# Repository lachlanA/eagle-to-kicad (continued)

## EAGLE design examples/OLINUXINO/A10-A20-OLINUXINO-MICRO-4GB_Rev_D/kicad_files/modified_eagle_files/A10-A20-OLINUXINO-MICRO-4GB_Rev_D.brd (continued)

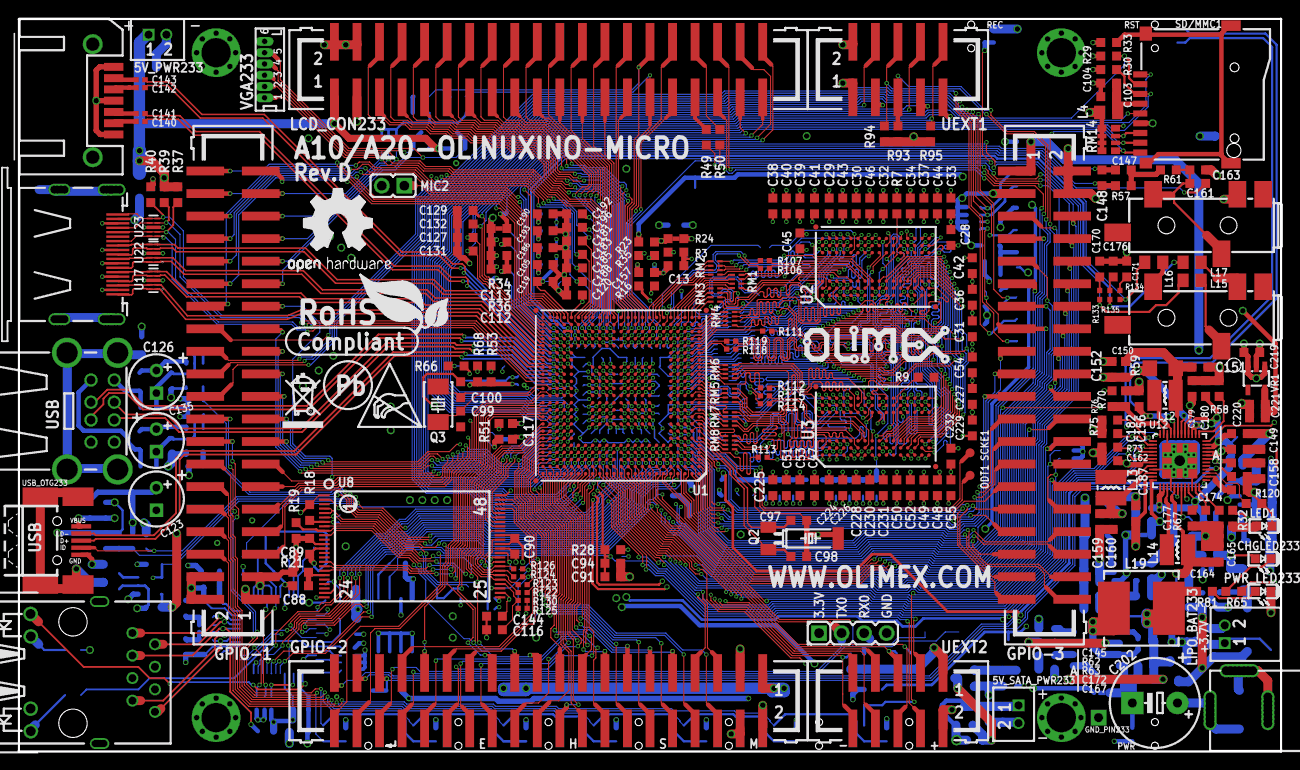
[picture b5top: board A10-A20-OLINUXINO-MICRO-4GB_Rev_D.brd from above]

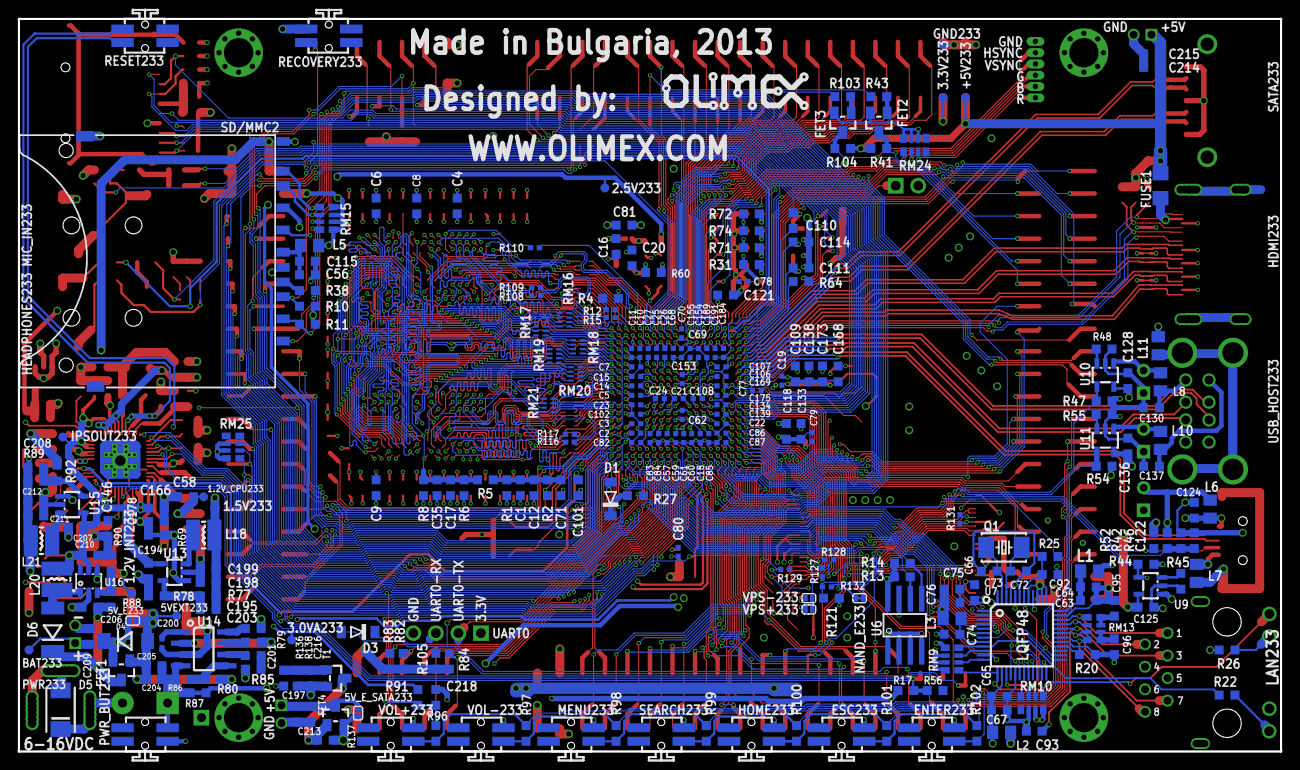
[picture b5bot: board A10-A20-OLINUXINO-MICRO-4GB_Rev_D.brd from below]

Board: 4 copper layers, 142.2 x 82.6 mm, 558 parts (271 on the bottom side), 539 nets.

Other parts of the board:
U$5: LOGO-OPENHARDWARE_8X8
U$6, U$8: OLIMEX1_V
U$9: PB
U$10: ESD_SYMBOL
U$11: RECYCLE_BIN1/8
U$12: ROHS

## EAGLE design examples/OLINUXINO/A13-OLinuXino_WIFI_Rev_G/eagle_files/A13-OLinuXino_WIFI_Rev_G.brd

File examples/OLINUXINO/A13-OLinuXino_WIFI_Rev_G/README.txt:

NOTE: ***** USE AT YOUR OWN RISK *****

This contains the eagle file's from OLIMEX/OLINUXINO from github, which have been Renumbered to work with KiCad
as KiCad will not work correctly with out parts reference ending in a number.
Also note the Eagle files have been converted to version 6.xx of eagle.

*** NOTE: you have to enable LIB prifix in the eagle6xx-sch-to-kicad-sch.ulp even thou is shows you don't need it.
          for some reson Ealge has a lib part which has the same name, as the ground part,  but dose not show up
          when the script searchs for conflicking part names, but show's up on the lib !!!  go figure !!!  ****

source of this project example is at Github address:
   https://github.com/OLIMEX/OLINUXINO/tree/master/HARDWARE/A13-OLinuXino

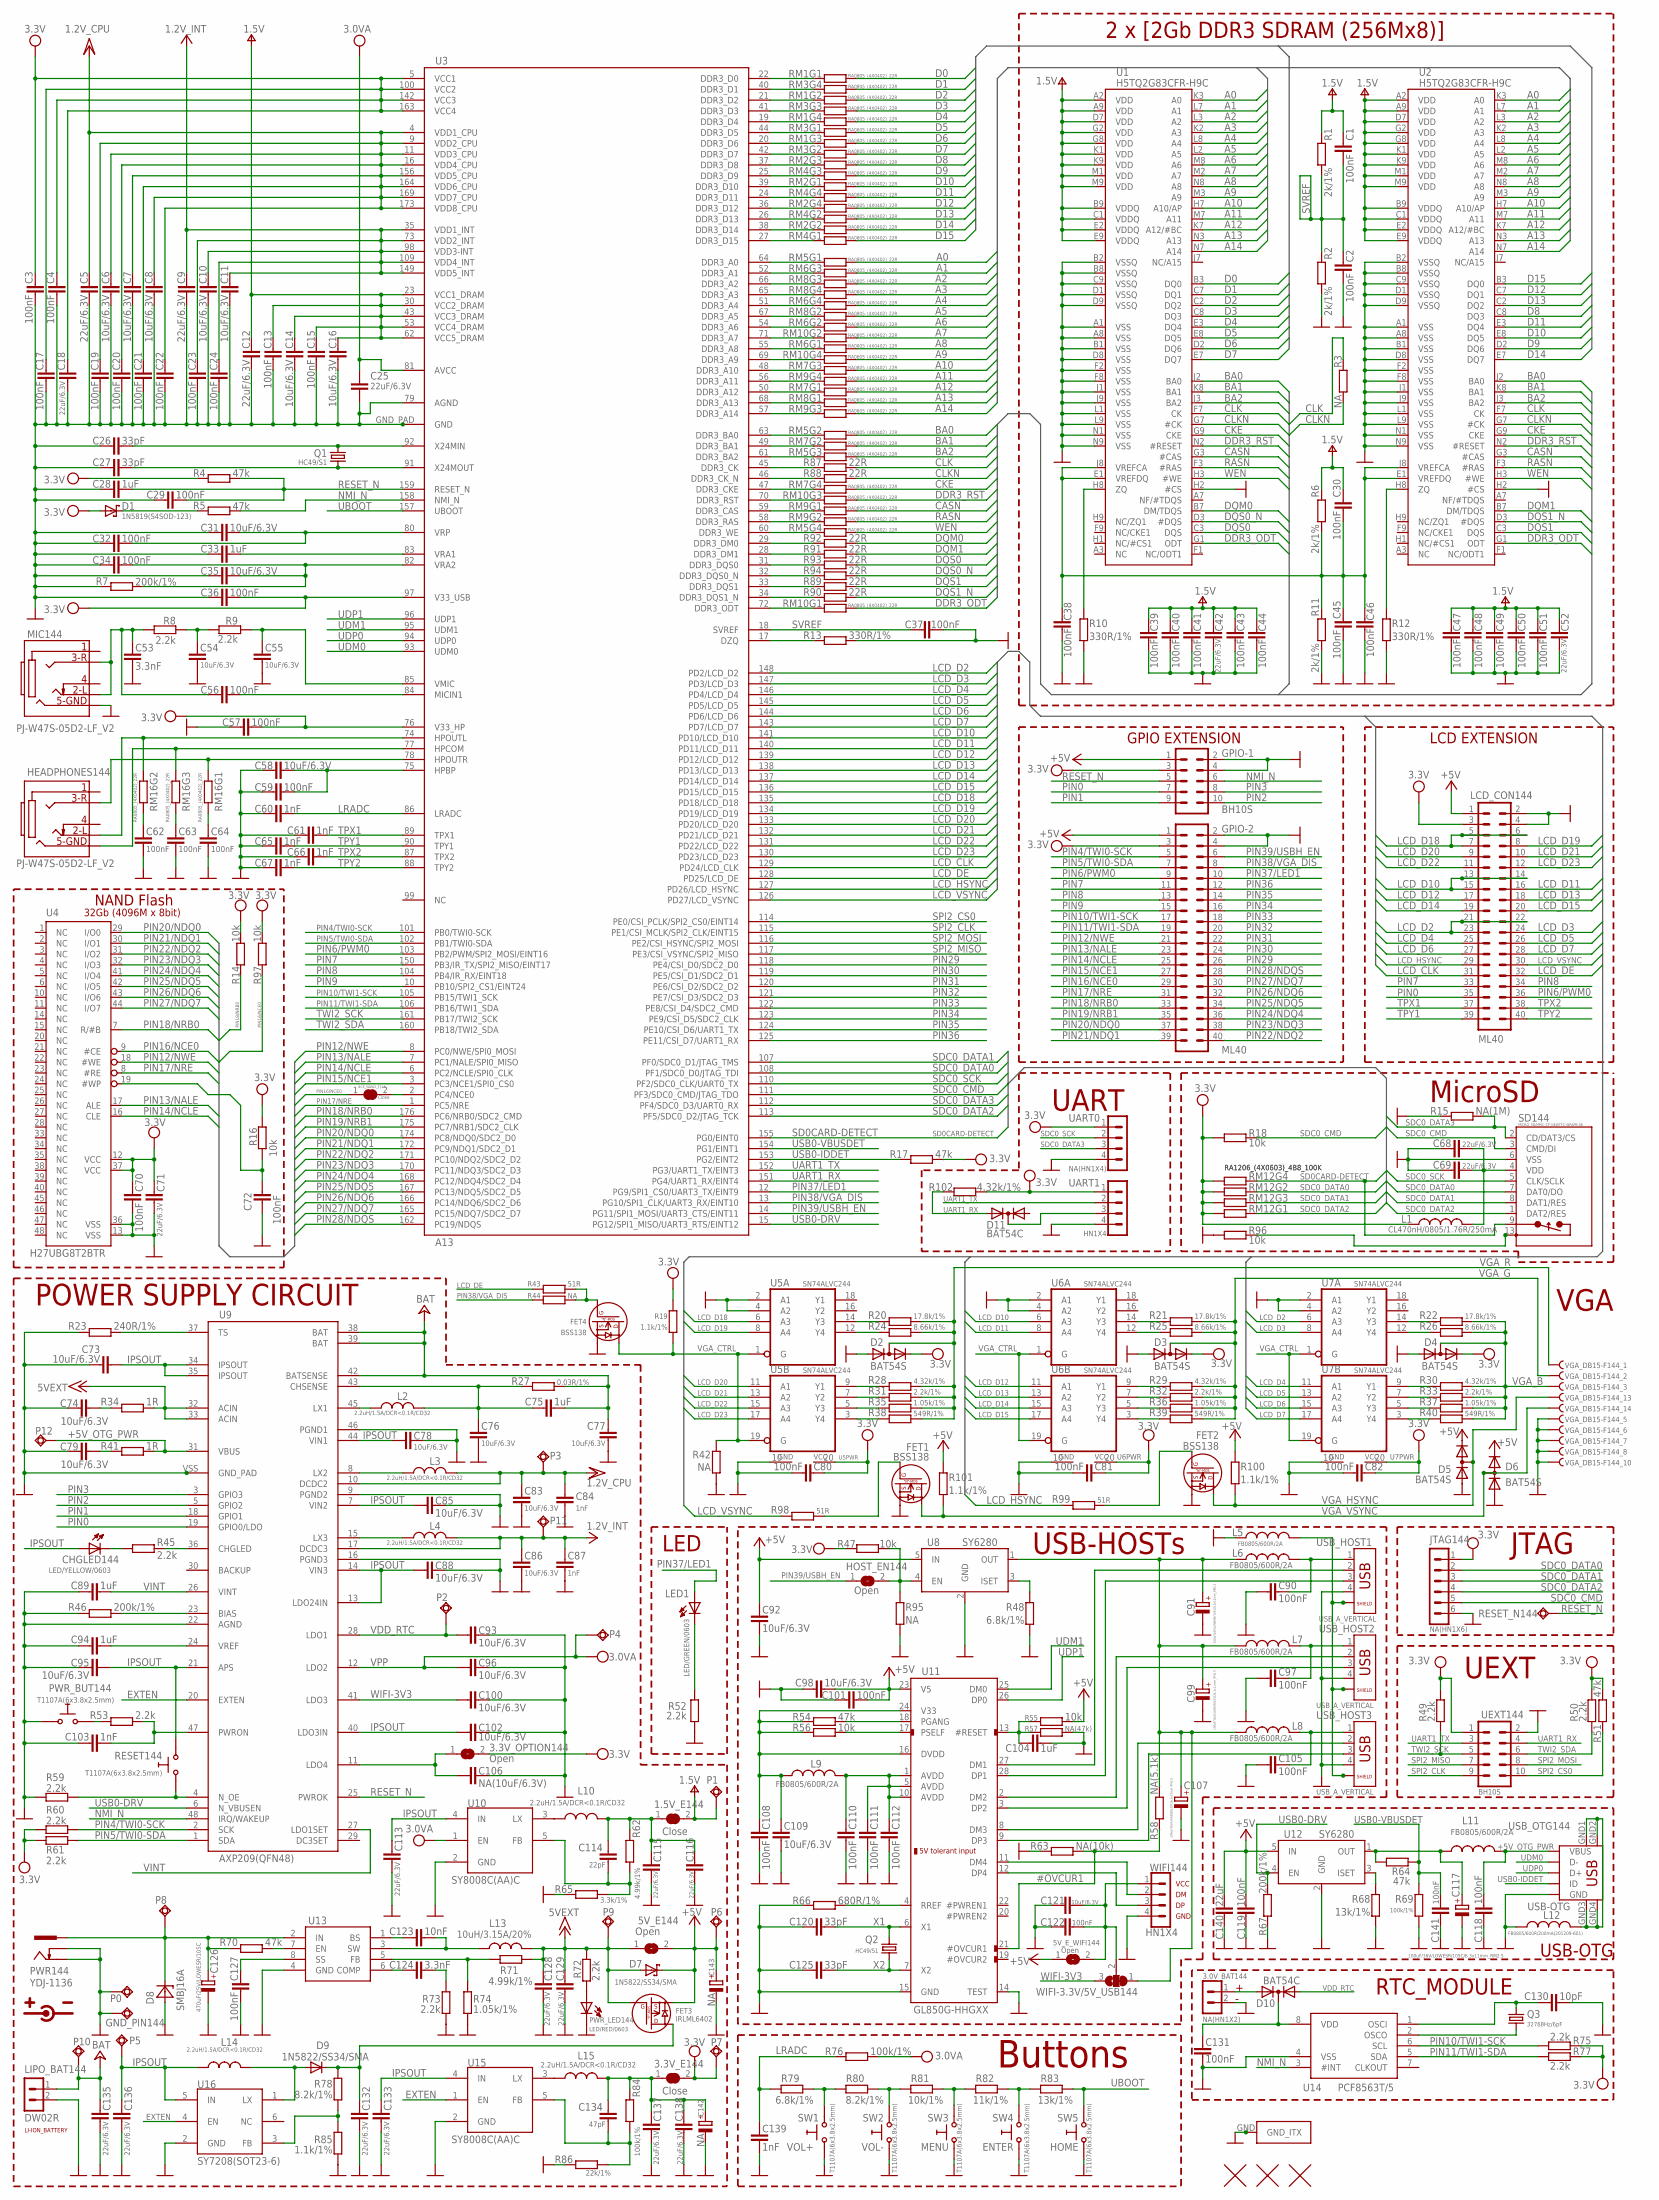
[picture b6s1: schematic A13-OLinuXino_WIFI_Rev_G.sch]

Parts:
1.5V_E144, 3.3V_E144: Close; SJ_1_SMALLER_CLOSE
3.0V_BAT144: NA(HN1X2); HN1X2
3.3V_OPTION144, 5V_E144, 5V_E_WIFI144: Open; SJ_1_SMALLER
#CE_NAND_E144: Close; SJ_1_SMALLER_CLOSE_10MILS
C1, C2, C3, C4, C13, C15, C17, C19, C20, C21, C22, C23, C24, C29, C30, C32, C34, C36, C37, C38, C39, C40, C41, C43, C44, C45, C46, C47, C48, C49, C50, C51, C56, C57, C59, C62, C63, C64, C70, C72, C80, C81, C82, C90, C97, C101, C105, C108, C110, C111, C112, C118, C119, C122, C127, C131, C141: 100nF; C0603_DWS
C5, C9, C12, C18, C25, C42, C52, C68, C69, C71, C113, C115, C116, C128, C129, C132, C133, C135, C136, C137, C138: 22uF/6.3V; C0603_DWS
C6, C7, C8, C10, C11, C14, C16, C31, C35, C54, C55, C58, C73, C74, C76, C77, C78, C79, C83, C85, C86, C88, C92, C93, C95, C96, C98, C100, C102, C109, C121: 10uF/6.3V; C0603_DWS
C26, C27, C120, C125: 33pF; C0603_DWS
C28, C33, C75, C89, C94, C104: 1uF; C0603_DWS
C53, C124: 3.3nF; C0603_DWS
C60, C61, C65, C66, C67, C84, C87, C103, C139: 1nF; C0603_DWS
C91, C99, C107, C117: 100uF/16V/LOWESR/105C/6.3x11mm_RM2.5; E2,5-6,3
C106: NA(10uF/6.3V); C0603_DWS
C114: 22pF; C0603_DWS
C123: 10nF; C0603_DWS
C126: 470uF/25V/LOWESR/105C; E5-10,5
C130: 10pF; C0603_DWS
C134: 47pF; C0603_DWS
C140: 22uF; C0603_DWS
C142, C143: NA; E3,5-8
CHGLED144: LED/YELLOW/0603; LED-0603
D1: 1N5819(S4SOD-123); SOD-123
D2, D3, D4, D5, D6: BAT54S; SOT23C(BAT54S)
D7: 1N5822/SS34/SMA; MLL-41
D8: SMBJ16A; DO214AA
D9: 1N5822/SS34/SMA; MELF-MLL41
D10, D11: BAT54C; SOT23C
FET1, FET2, FET4: BSS138; SOT23
FET3: IRLML6402; SOT23
GND_PIN144: TESTPAD3; TEST_PAD40/70/SQUARE
GPIO-1: BH10S; ML10-MALE
GPIO-2: ML40
HEADPHONES144: PJ-W47S-05D2-LF_V2; PJ-W47S-05D2-LF_5PIN_V2
HOST_EN144: Open; SJ_1_SMALLER
JTAG144: NA(HN1X6); HN1X6
L1: CL470nH/0805/1.76R/250mA; L0805_5MIL_DWS
L2, L3, L4, L10, L14, L15: 2.2uH/1.5A/DCR<0.1R/CD32; CD32
L5, L6, L7, L8, L9, L11: FB0805/600R/2A; L0805_5MIL_DWS
L12: FB0805/600R/200mA(201209-601); L0805_5MIL_DWS
L13: 10uH/3.15A/20%; 8X8MM_3131
LCD_CON144: ML40
LED1: LED/GREEN/0603; LED-0603
LIPO_BAT144: DW02R
MIC144: PJ-W47S-05D2-LF_V2; PJ-W47S-05D2-LF_5PIN_V2
P0, P1, P2, P3, P4, P5, P6, P7, P8, P9, P10, P11, P12: TESTPADTESTPAD_40-ROUND; TESTPAD_40-ROUND
PWR144: YDJ-1136; PWR_JACK_UNI_MILLING
PWR_BUT144: T1107A(6x3.8x2.5mm); SW-TAKT_6X3.5_SMD
PWR_LED144: LED/RED/0603; LED-0603
Q1, Q2: HC49/S1; HC49/SMD2_THIN
Q3: 32768Hz/6pF; MC-306
R1, R2, R6, R11: 2k/1%; R0603_5MIL_DWS
R3, R42, R44, R95: NA; R0603_5MIL_DWS
R4, R5, R17, R51, R54, R64, R70: 47k; R0603_5MIL_DWS
R7, R46, R67: 200k/1%; R0603_5MIL_DWS
R8, R9, R45, R49, R50, R52, R53, R59, R60, R61, R72, R73, R75, R77: 2.2k; R0603_5MIL_DWS
R10, R12, R13: 330R/1%; R0603_5MIL_DWS
R14, R16, R18, R47, R55, R56, R96, R97: 10k; R0603_5MIL_DWS
R15: NA(1M); R0603_5MIL_DWS
R19, R85, R100, R101: 1.1k/1%; R0603_5MIL_DWS
R20, R21, R22: 17.8k/1%; R0603_5MIL_DWS
R23: 240R/1%; R0603_5MIL_DWS
R24, R25, R26: 8.66k/1%; R0603_5MIL_DWS
R27: 0.03R/1%; R1206_5MIL_WS
R28, R29, R30, R102: 4.32k/1%; R0603_5MIL_DWS
R31, R32, R33: 2.2k/1%; R0603_5MIL_DWS
R34, R41: 1R; R0603_5MIL_DWS
R35, R36, R37, R74: 1.05k/1%; R0603_5MIL_DWS
R38, R39, R40: 549R/1%; R0603_5MIL_DWS
R43, R98, R99: 51R; R0603_5MIL_DWS
R48, R79: 6.8k/1%; R0603_5MIL_DWS
R57: NA(47k); R0603_5MIL_DWS
R58: NA(5.1k); R0603_5MIL_DWS
R62, R71: 4.99k/1%; R0603_5MIL_DWS
R63: NA(10k); R0603_5MIL_DWS
R65: 3.3k/1%; R0603_5MIL_DWS
R66: 680R/1%; R0603_5MIL_DWS
R68, R83: 13k/1%; R0603_5MIL_DWS
R69, R76, R84: 100k/1%; R0603_5MIL_DWS
R78, R80: 8.2k/1%; R0603_5MIL_DWS
R81: 10k/1%; R0603_5MIL_DWS
R82: 11k/1%; R0603_5MIL_DWS
R86: 22k/1%; R0603_5MIL_DWS
R87, R88, R89, R90, R91, R92, R93, R94: 22R; R0603_5MIL_DWS
RESET144: T1107A(6x3.8x2.5mm); SW-TAKT_6X3.5_SMD
RESET_N144: TESTPAD40/70; TESTPAD
RM1, RM2, RM3, RM4, RM5, RM6, RM7, RM8, RM9, RM10, RM16: RA0805_(4X0402)_22R; R_MATRIX_4_0402_25X625
RM12: RA1206_(4X0603)_4B8_100K; R_MATRIX_4
SD144: MICRO_SD/MMC_CP_NEWTFC-WPAPR-08; TFC-WPAPR-08
SW1, SW2, SW3, SW4, SW5: T1107A(6x3.8x2.5mm); SW-TAKT_6X3.5_SMD
U1, U2: H5TQ2G83CFR-H9C; FBGA78
U3: A13; TQFP176
U4: H27UBG8T2BTR; TSOP48
U5, U6, U7: SN74ALVC244; PW
U8, U12: SY6280; SOT23-5
U9: AXP209(QFN48); QFN48
U10, U15: SY8008C(AA)C; SOT23-5
U11: GL850G-HHGXX; SSOP28
U13: MP1482DS; SOIC8
U14: PCF8563T/5; SO-8
U16: SY7208(SOT23-6); SOT23-6
U$1, U$2, U$3: FIDUCIAL1X2; FIDUCIAL-1X2
U$4: NANO_ITX; NANO-ITX_120X120
UART0: NA(HN1X4); HN1X4
UART1: HN1X4
UEXT144: BH10S; ML10-MALE
USB_HOST1, USB_HOST2, USB_HOST3: USB_A_VERTICAL; USB_A_VERTICAL_PTH
USB_OTG144: USB-OTG; USB_MINI_9PIN
VGA_DB15-F144: VGA15; DB15-F_22MM
WIFI144: HN1X4
WIFI-3.3V/5V_USB144: SJ2W6; SJ_2_SMALL_12_TIED

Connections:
#OVCUR1: R58.1, R63.2, U11.21 (#OVCUR1)
+5V: 5V_E144.2, 5V_E_WIFI144.1, C92.1, C98.1, C101.1, C119.1, C140.1, C143.+, D5.2 (K), D6.2 (K), D7.K (C), FET3.2 (S), GPIO-1.1, GPIO-2.1, LCD_CON144.1, P6.1, R55.2, R100.2, R101.2, U8.5 (IN), U11.23 (V5), U12.5 (IN)
+5V_OTG_PWR: C118.1, L11.1, P12.1, R41.2, U9.31 (VBUS), USB_OTG144.VBUS
+15V: 5V_E144.1, C128.1, C129.1, D7.A, FET3.1 (G), L13.2, P9.1, R34.2, R71.2, R72.1, U9.32 (ACIN), U9.33 (ACIN)
+24V: C75.2, C77.1, C135.2, LIPO_BAT144.1, P10.1, R27.2, U9.38 (BAT), U9.39 (BAT), U9.42 (BATSENSE)
A0: RM5.1.2 (2), U1.K3 (A0), U2.K3 (A0)
A1: RM6.3.2 (2), U1.L7 (A1), U2.L7 (A1)
A2: RM8.3.2 (2), U1.L3 (A2), U2.L3 (A2)
A3: RM8.4.2 (2), U1.K2 (A3), U2.K2 (A3)
A4: RM6.4.2 (2), U1.L8 (A4), U2.L8 (A4)
A5: RM8.2.2 (2), U1.L2 (A5), U2.L2 (A5)
A6: RM6.2.2 (2), U1.M8 (A6), U2.M8 (A6)
A7: RM10.2.2 (2), U1.M2 (A7), U2.M2 (A7)
A8: RM6.1.2 (2), U1.N8 (A8), U2.N8 (A8)
A9: RM10.4.2 (2), U1.M3 (A9), U2.M3 (A9)
A10: RM7.3.2 (2), U1.H7 (A10/AP), U2.H7 (A10/AP)
A11: RM9.4.2 (2), U1.M7 (A11), U2.M7 (A11)
A12: RM7.1.2 (2), U1.K7 (A12/#BC), U2.K7 (A12/#BC)
A13: RM8.1.2 (2), U1.N3 (A13), U2.N3 (A13)
A14: RM9.3.2 (2), U1.N7 (A14), U2.N7 (A14)
AVDD: C110.1, C111.1, C112.1, L9.2, U11.1 (AVDD), U11.5 (AVDD), U11.10 (AVDD)
BA0: RM5.2.2 (2), U1.J2 (BA0), U2.J2 (BA0)
BA1: RM7.2.2 (2), U1.K8 (BA1), U2.K8 (BA1)
BA2: RM5.3.2 (2), U1.J3 (BA2), U2.J3 (BA2)
CASN: RM9.1.2 (2), U1.G3 (#CAS), U2.G3 (#CAS)
CKE: RM7.4.2 (2), U1.G9 (CKE), U2.G9 (CKE)
CLK: R3.2, R87.1, U1.F7 (CK), U2.F7 (CK)
CLKN: R3.1, R88.1, U1.G7 (#CK), U2.G7 (#CK)
D0: RM1.1.2 (2), U1.B3 (DQ0)
D1: RM3.4.2 (2), U1.C7 (DQ1)
D2: RM1.2.2 (2), U1.C2 (DQ2)
D3: RM3.3.2 (2), U1.C8 (DQ3)
D4: RM1.4.2 (2), U1.E3 (DQ4)
D5: RM3.1.2 (2), U1.E8 (DQ5)
D6: RM1.3.2 (2), U1.D2 (DQ6)
D7: RM3.2.2 (2), U1.E7 (DQ7)
D8: RM2.3.2 (2), U2.C8 (DQ3)
D9: RM4.3.2 (2), U2.D2 (DQ6)
D10: RM2.1.2 (2), U2.E8 (DQ5)
D11: RM4.4.2 (2), U2.E3 (DQ4)
D12: RM2.4.2 (2), U2.C7 (DQ1)
D13: RM4.2.2 (2), U2.C2 (DQ2)
D14: RM2.2.2 (2), U2.E7 (DQ7)
D15: RM4.1.2 (2), U2.B3 (DQ0)
DDR3_A0: RM5.1.1 (1), U3.64 (DDR3_A0)
DDR3_A1: RM6.3.1 (1), U3.52 (DDR3_A1)
DDR3_A2: RM8.3.1 (1), U3.66 (DDR3_A2)
DDR3_A3: RM8.4.1 (1), U3.65 (DDR3_A3)
DDR3_A4: RM6.4.1 (1), U3.51 (DDR3_A4)
DDR3_A5: RM8.2.1 (1), U3.67 (DDR3_A5)
DDR3_A6: RM6.2.1 (1), U3.54 (DDR3_A6)
DDR3_A7: RM10.2.1 (1), U3.71 (DDR3_A7)
DDR3_A8: RM6.1.1 (1), U3.55 (DDR3_A8)
DDR3_A9: RM10.4.1 (1), U3.69 (DDR3_A9)
DDR3_A10: RM7.3.1 (1), U3.48 (DDR3_A10)
DDR3_A11: RM9.4.1 (1), U3.56 (DDR3_A11)
DDR3_A12: RM7.1.1 (1), U3.50 (DDR3_A12)
DDR3_A13: RM8.1.1 (1), U3.68 (DDR3_A13)
DDR3_A14: RM9.3.1 (1), U3.57 (DDR3_A14)
DDR3_BA0: RM5.2.1 (1), U3.63 (DDR3_BA0)
DDR3_BA1: RM7.2.1 (1), U3.49 (DDR3_BA1)
DDR3_BA2: RM5.3.1 (1), U3.61 (DDR3_BA2)
DDR3_CAS: RM9.1.1 (1), U3.59 (DDR3_CAS)
DDR3_CK: R87.2, U3.45 (DDR3_CK)
DDR3_CKE: RM7.4.1 (1), U3.47 (DDR3_CKE)
DDR3_CK_N: R88.2, U3.46 (DDR3_CK_N)
DDR3_D0: RM1.1.1 (1), U3.22 (DDR3_D0)
DDR3_D1: RM3.4.1 (1), U3.40 (DDR3_D1)
DDR3_D2: RM1.2.1 (1), U3.21 (DDR3_D2)
DDR3_D3: RM3.3.1 (1), U3.41 (DDR3_D3)
DDR3_D4: RM1.4.1 (1), U3.19 (DDR3_D4)
DDR3_D5: RM3.1.1 (1), U3.44 (DDR3_D5)
DDR3_D6: RM1.3.1 (1), U3.20 (DDR3_D6)
DDR3_D7: RM3.2.1 (1), U3.42 (DDR3_D7)
DDR3_D8: RM2.3.1 (1), U3.37 (DDR3_D8)
DDR3_D9: RM4.3.1 (1), U3.25 (DDR3_D9)
DDR3_D10: RM2.1.1 (1), U3.39 (DDR3_D10)
DDR3_D11: RM4.4.1 (1), U3.24 (DDR3_D11)
DDR3_D12: RM2.4.1 (1), U3.36 (DDR3_D12)
DDR3_D13: RM4.2.1 (1), U3.26 (DDR3_D13)
DDR3_D14: RM2.2.1 (1), U3.38 (DDR3_D14)
DDR3_D15: RM4.1.1 (1), U3.27 (DDR3_D15)
DDR3_DM0: R92.2, U3.29 (DDR3_DM0)
DDR3_DM1: R91.2, U3.28 (DDR3_DM1)
DDR3_DQS0: R93.2, U3.31 (DDR3_DQS0)
DDR3_DQS0_N: R94.2, U3.32 (DDR3_DQS0_N)
DDR3_DQS1: R89.2, U3.33 (DDR3_DQS1)
DDR3_DQS1_N: R90.2, U3.34 (DDR3_DQS1_N)
DDR3_ODT: RM10.1.2 (2), U1.G1 (ODT), U2.G1 (ODT)
DDR3_ODTT: RM10.1.1 (1), U3.72 (DDR3_ODT)
DDR3_RAS: RM9.2.1 (1), U3.58 (DDR3_RAS)
DDR3_RST: RM10.3.2 (2), U1.N2 (#RESET), U2.N2 (#RESET)
DDR3_RSTT: RM10.3.1 (1), U3.70 (DDR3_RST)
DDR3_WE: RM5.4.1 (1), U3.60 (DDR3_WE)
DM1: U11.27 (DM1), USB_HOST1.2
DM2: U11.2 (DM2), USB_HOST2.2
DM3: U11.8 (DM3), USB_HOST3.2
DM4: U11.11 (DM4), WIFI144.2
DP1: U11.28 (DP1), USB_HOST1.3
DP2: U11.3 (DP2), USB_HOST2.3
DP3: U11.9 (DP3), USB_HOST3.3
DP4: U11.12 (DP4), WIFI144.3
DQM0: R92.1, U1.B7 (DM/TDQS)
DQM1: R91.1, U2.B7 (DM/TDQS)
DQS0: R93.1, U1.C3 (DQS)
DQS0_N: R94.1, U1.D3 (#DQS)
DQS1: R89.1, U2.C3 (DQS)
DQS1_N: R90.1, U2.D3 (#DQS)
DVDD: C108.1, C109.1, L9.1, R54.1, R56.1, U11.16 (DVDD), U11.24 (V33)
DZQ: R13.2, U3.17 (DZQ)
EXTEN: U9.20 (EXTEN), U15.1 (EN), U16.4 (EN)
GND: 3.0V_BAT144.2, C2.1, C3.1, C4.1, C5.1, C6.1, C7.1, C8.1, C9.1, C10.1, C11.1, C12.1, C13.1, C14.1, C15.1, C16.1, C17.1, C18.1, C19.1, C20.1, C21.1, C22.1, C23.1, C24.1, C25.1, C26.1, C27.1, C28.1, C29.1, C31.1, C32.1, C33.1, C34.1, C35.1, C36.1, C37.1, C38.1, C39.1, C40.1, C41.1, C42.1, C43.1, C44.1, C45.1, C46.1, C47.1, C48.1, C49.1, C50.1, C51.1, C52.1, C53.1, C54.1, C55.1, C57.1, C58.1, C59.1, C60.1, C61.1, C62.1, C63.1, C64.1, C65.1, C66.1, C67.1, C68.1, C69.1, C70.1, C71.1, C72.1, C73.1, C74.1, C76.2, C77.2, C78.2, C79.1, C80.2, C81.2, C82.2, C83.2, C84.2, C85.2, C86.2, C87.2, C88.2, C89.1, C90.2, C91.-, C92.2, C93.2, C94.1, C95.1, C96.2, C97.2, C98.2, C99.-, C100.2, C101.2, C102.2, C103.1, C104.1, C105.2, C106.2, C107.-, C108.2, C109.2, C110.2, C111.2, C112.2, C113.2, C115.2, C116.2, C117.-, C118.2, C119.2, C120.1, C121.2, C122.2, C125.1, C126.-, C127.2, C128.2, C129.2, C130.2, C131.1, C132.2, C133.2, C135.1, C136.1, C137.2, C138.2, C139.2, C140.2, C141.2, C142.-, C143.-, D2.1 (A), D3.1 (A), D4.1 (A), D5.1 (A), D6.1 (A), D8.A, FET1.2 (S)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
IPSOUT: C73.2, C78.1, C85.1, C88.1, C95.2, C102.1, C113.1, C133.1, C136.2, CHGLED144.A, L14.1, P5.1, RESET144.P$2 (1), U9.7 (VIN2), U9.13 (LDO24IN), U9.14 (VIN3), U9.21 (APS), U9.34 (IPSOUT), U9.35 (IPSOUT), U9.40 (LDO3IN), U9.44 (VIN1), U10.4 (IN), U15.4 (IN), U16.5 (IN)
LCD_CLK: LCD_CON144.31, U3.129 (PD24/LCD_CLK)
LCD_D2: LCD_CON144.21, LCD_CON144.22, LCD_CON144.23, U3.148 (PD2/LCD_D2), U7.6 (A3)
LCD_D3: LCD_CON144.24, U3.147 (PD3/LCD_D3), U7.8 (A4)
LCD_D4: LCD_CON144.25, U3.146 (PD4/LCD_D4), U7.11 (A1)
LCD_D5: LCD_CON144.26, U3.145 (PD5/LCD_D5), U7.13 (A2)
LCD_D6: LCD_CON144.27, U3.144 (PD6/LCD_D6), U7.15 (A3)
LCD_D7: LCD_CON144.28, U3.143 (PD7/LCD_D7), U7.17 (A4)
LCD_D10: LCD_CON144.13, LCD_CON144.14, LCD_CON144.15, U3.141 (PD10/LCD_D10), U6.6 (A3)
LCD_D11: LCD_CON144.16, U3.140 (PD11/LCD_D11), U6.8 (A4)
LCD_D12: LCD_CON144.17, U3.139 (PD12/LCD_D12), U6.11 (A1)
LCD_D13: LCD_CON144.18, U3.138 (PD13/LCD_D13), U6.13 (A2)
LCD_D14: LCD_CON144.19, U3.137 (PD14/LCD_D14), U6.15 (A3)
LCD_D15: LCD_CON144.20, U3.136 (PD15/LCD_D15), U6.17 (A4)
LCD_D18: LCD_CON144.5, LCD_CON144.6, LCD_CON144.7, U3.135 (PD18/LCD_D18), U5.6 (A3)
LCD_D19: LCD_CON144.8, U3.134 (PD19/LCD_D19), U5.8 (A4)
LCD_D20: LCD_CON144.9, U3.133 (PD20/LCD_D20), U5.11 (A1)
LCD_D21: LCD_CON144.10, U3.132 (PD21/LCD_D21), U5.13 (A2)
LCD_D22: LCD_CON144.11, U3.131 (PD22/LCD_D22), U5.15 (A3)
LCD_D23: LCD_CON144.12, U3.130 (PD23/LCD_D23), U5.17 (A4)
LCD_DE: LCD_CON144.32, R43.1, U3.128 (PD25/LCD_DE)
LCD_HSYNC: LCD_CON144.29, R99.1, U3.127 (PD26/LCD_HSYNC)
LCD_VSYNC: LCD_CON144.30, R98.1, U3.126 (PD27/LCD_VSYNC)
LRADC: C60.2, C139.1, R76.2, R79.1, U3.86 (LRADC)
unnamed: C58.2, C59.2, U3.75 (HPBP)
unnamed: C30.2, C38.2, C45.2, C46.2, R6.1, R11.2, U1.E1 (VREFDQ), U1.J8 (VREFCA), U2.E1 (VREFDQ), U2.J8 (VREFCA)
unnamed: R10.2, U1.H8 (ZQ)
unnamed: R45.2, U9.36 (CHGLED)
unnamed: R12.2, U2.H8 (ZQ)
unnamed: HOST_EN144.2, R47.2, R95.2, U8.4 (EN)
unnamed: R96.1, SD144.10 (PACK1), SD144.11 (PACK2), SD144.12 (PACK3), SD144.13 (PACK4)
unnamed: L10.1, U10.3 (LX)
unnamed: C31.2, C32.2, U3.80 (VRP)
unnamed: D1.C, R5.2
unnamed: 5V_E_WIFI144.2, C121.1, C122.1, WIFI144.1, WIFI-3.3V/5V_USB144.2
unnamed: #CE_NAND_E144.2, U3.2 (PC4/NCE0)
unnamed: C33.2, U3.83 (VRA1)
unnamed: C34.2, C35.2, R7.1, U3.82 (VRA2)
unnamed: FET1.1 (G), R98.2
unnamed: C53.2, C56.1, MIC144.2, MIC144.3, R8.2
unnamed: FET2.1 (G), R99.2
unnamed: 1.5V_E144.1, C114.1, C115.1, C116.1, L10.2, R62.1
unnamed: C114.2, R62.2, R65.1, U10.5 (FB)
unnamed: R37.1, U7.5 (Y3)
unnamed: FET4.1 (G), R43.2, R44.1
unnamed: C54.2, R8.1, R9.2
unnamed: C132.1, D9.1 (C), FET3.3 (D), R78.2
unnamed: C131.2, D10.3 (K), U14.8 (VDD)
unnamed: C56.2, U3.84 (MICIN1)
unnamed: HEADPHONES144.2, RM16.2.2 (2), U3.74 (HPOUTL)
unnamed: HEADPHONES144.5, RM16.3.2 (2), U3.77 (HPCOM)
unnamed: HEADPHONES144.3, RM16.1.2 (2), U3.78 (HPOUTR)
unnamed: 3.0V_BAT144.1, D10.2 (A2)
unnamed: D11.3 (K), UART1.3
unnamed: C126.+, D8.C, P8.1, PWR144.+, R70.1, U13.2 (IN)
unnamed: C62.2, RM16.2.1 (1)
unnamed: C63.2, RM16.3.1 (1)
unnamed: C127.1, U13.8 (SS)
unnamed: R70.2, U13.7 (EN)
unnamed: PWR_BUT144.P$2 (1), R53.1
unnamed: LED1.C, R52.2
unnamed: CHGLED144.C, R45.1
unnamed: C64.2, RM16.1.1 (1)
unnamed: C123.1, U13.1 (BS)
unnamed: C123.2, L13.1, U13.3 (SW)
unnamed: C124.1, U13.6 (COMP)
unnamed: C124.2, R73.1
unnamed: R71.1, R74.1, U13.5 (FB)
unnamed: L15.1, U15.3 (LX)
unnamed: 3.3V_E144.1, C134.1, C137.1, C138.1, C142.+, L15.2, R84.1
unnamed: C134.2, R84.2, R86.1, U15.5 (FB)
unnamed: R79.2, R80.1, SW1.P$2 (1)
unnamed: R80.2, R81.1, SW2.P$2 (1)
unnamed: R81.2, R82.1, SW3.P$2 (1)
unnamed: R82.2, R83.1, SW4.P$2 (1)
unnamed: R68.2, U12.3 (ISET)
unnamed: C117.+, L11.2, R64.2, U12.1 (OUT)
unnamed: R48.2, U8.3 (ISET)
unnamed: R66.2, U11.4 (RREF)
unnamed: R40.1, U7.3 (Y4)
unnamed: R30.1, U7.9 (Y1)
unnamed: R54.2, U11.18 (PGANG)
unnamed: R56.2, U11.17 (PSELF)
unnamed: R33.1, U7.7 (Y2)
unnamed: R22.1, U7.14 (Y3)
unnamed: R26.1, U7.12 (Y4)
unnamed: L5.2, USB_HOST1.P$3 (5), USB_HOST1.P$4 (6), USB_HOST2.P$3 (5), USB_HOST2.P$4 (6), USB_HOST3.P$3 (5), USB_HOST3.P$4 (6)
unnamed: C90.1, L6.2, USB_HOST1.1
unnamed: C97.1, L7.2, USB_HOST2.1
unnamed: C105.1, L8.2, USB_HOST3.1
unnamed: C91.+, C99.+, C107.+, L6.1, L7.1, L8.1, R58.2, U8.1 (OUT), WIFI-3.3V/5V_USB144.1
unnamed: R29.1, U6.9 (Y1)
unnamed: R32.1, U6.7 (Y2)
unnamed: C104.2, R55.1, R57.1, U11.13 (#RESET)
unnamed: R46.2, U9.23 (BIAS)
unnamed: C130.1, Q3.1, U14.1 (OSCI)
unnamed: Q3.4 (2), U14.2 (OSCO)
unnamed: D9.2 (A), L14.2, U16.1 (LX)
unnamed: C72.2, R16.2, U4.19 (#WP)
unnamed: R23.2, U9.37 (TS)
unnamed: R78.1, R85.1, U16.3 (FB)
unnamed: L2.1, U9.45 (LX1)
unnamed: C75.1, C76.1, L2.2, R27.1, U9.43 (CHSENSE)
unnamed: PWR_LED144.A, R72.2
unnamed: L3.1, U9.8 (LX2)
unnamed: L4.1, U9.15 (LX3)
unnamed: C94.2, U9.24 (VREF)
unnamed: 3.3V_OPTION144.1, C106.1, U9.11 (LDO4)
unnamed: C74.2, R34.1
unnamed: C79.2, R41.1
unnamed: R36.1, U6.5 (Y3)
unnamed: C103.2, R53.2, U9.47 (PWRON)
unnamed: R59.2, RESET144.P$1 (0), U9.4 (N_OE)
unnamed: R39.1, U6.3 (Y4)
unnamed: R21.1, U6.14 (Y3)
unnamed: R25.1, U6.12 (Y4)
unnamed: R28.1, U5.9 (Y1)
unnamed: R31.1, U5.7 (Y2)
unnamed: R35.1, U5.5 (Y3)
unnamed: R38.1, U5.3 (Y4)
unnamed: R20.1, U5.14 (Y3)
unnamed: R24.1, U5.12 (Y4)
unnamed: L12.2, USB_OTG144.GND1, USB_OTG144.GND2, USB_OTG144.GND3, USB_OTG144.GND4
NMI_N: GPIO-1.6, R5.1, U3.158 (NMI_N), U9.48 (IRQ/WAKEUP), U14.3 (#INT)
PIN0: GPIO-1.7, LCD_CON144.35, U9.19 (GPIO0/LDO)
PIN1: GPIO-1.9, U9.18 (GPIO1)
PIN2: GPIO-1.10, U9.5 (GPIO2)
PIN3: GPIO-1.8, U9.3 (GPIO3)
PIN4/TWI0-SCK: GPIO-2.5, R60.1, U3.101 (PB0/TWI0-SCK), U9.2 (SCK)
PIN5/TWI0-SDA: GPIO-2.7, R61.1, U3.102 (PB1/TWI0-SDA), U9.1 (SDA)
PIN6/PWM0: GPIO-2.9, LCD_CON144.36, U3.103 (PB2/PWM/SPI2_MOSI/EINT16)
PIN7: GPIO-2.11, LCD_CON144.33, U3.150 (PB3/IR_TX/SPI2_MISO/EINT17)
PIN8: GPIO-2.13, LCD_CON144.34, U3.104 (PB4/IR_RX/EINT18)
PIN9: GPIO-2.15, U3.10 (PB10/SPI2_CS1/EINT24)
PIN10/TWI1-SCK: GPIO-2.17, R75.1, U3.105 (PB15/TWI1_SCK), U14.6 (SCL)
PIN11/TWI1-SDA: GPIO-2.19, R77.1, U3.106 (PB16/TWI1_SDA), U14.5 (SDA)
PIN12/NWE: GPIO-2.21, U3.8 (PC0/NWE/SPI0_MOSI), U4.18 (#WE)
PIN13/NALE: GPIO-2.23, U3.7 (PC1/NALE/SPI0_MISO), U4.17 (ALE)
PIN14/NCLE: GPIO-2.25, U3.6 (PC2/NCLE/SPI0_CLK), U4.16 (CLE)
PIN15/NCE1: GPIO-2.27, U3.3 (PC3/NCE1/SPI0_CS0)
PIN16/NCE0: #CE_NAND_E144.1, GPIO-2.29, R97.2, U4.9 (#CE)
PIN17/NRE: GPIO-2.31, U3.1 (PC5/NRE), U4.8 (#RE)
PIN18/NRB0: GPIO-2.33, R14.2, U3.176 (PC6/NRB0/SDC2_CMD), U4.7 (R/#B)
PIN19/NRB1: GPIO-2.35, U3.175 (PC7/NRB1/SDC2_CLK)
PIN20/NDQ0: GPIO-2.37, U3.174 (PC8/NDQ0/SDC2_D0), U4.29 (I/O0)
PIN21/NDQ1: GPIO-2.39, U3.172 (PC9/NDQ1/SDC2_D1), U4.30 (I/O1)
PIN22/NDQ2: GPIO-2.40, U3.171 (PC10/NDQ2/SDC2_D2), U4.31 (I/O2)
PIN23/NDQ3: GPIO-2.38, U3.170 (PC11/NDQ3/SDC2_D3), U4.32 (I/O3)
PIN24/NDQ4: GPIO-2.36, U3.168 (PC12/NDQ4/SDC2_D4), U4.41 (I/O4)
PIN25/NDQ5: GPIO-2.34, U3.167 (PC13/NDQ5/SDC2_D5), U4.42 (I/O5)
PIN26/NDQ6: GPIO-2.32, U3.166 (PC14/NDQ6/SDC2_D6), U4.43 (I/O6)
PIN27/NDQ7: GPIO-2.30, U3.165 (PC15/NDQ7/SDC2_D7), U4.44 (I/O7)
PIN28/NDQS: GPIO-2.28, U3.162 (PC19/NDQS)
PIN29: GPIO-2.26, U3.118 (PE4/CSI_D0/SDC2_D0)
PIN30: GPIO-2.24, U3.119 (PE5/CSI_D1/SDC2_D1)
PIN31: GPIO-2.22, U3.120 (PE6/CSI_D2/SDC2_D2)
PIN32: GPIO-2.20, U3.121 (PE7/CSI_D3/SDC2_D3)
PIN33: GPIO-2.18, U3.122 (PE8/CSI_D4/SDC2_CMD)
PIN34: GPIO-2.16, U3.123 (PE9/CSI_D5/SDC2_CLK)
PIN35: GPIO-2.14, U3.124 (PE10/CSI_D6/UART1_TX)
PIN36: GPIO-2.12, U3.125 (PE11/CSI_D7/UART1_RX)
PIN37/LED1: GPIO-2.10, LED1.A, U3.12 (PG9/SPI1_CS0/UART3_TX/EINT9)
PIN38/VGA_DIS: GPIO-2.8, R44.2, U3.13 (PG10/SPI1_CLK/UART3_RX/EINT10)
PIN39/USBH_EN: GPIO-2.6, HOST_EN144.1, U3.14 (PG11/SPI1_MOSI/UART3_CTS/EINT11)
RASN: RM9.2.2 (2), U1.F3 (#RAS), U2.F3 (#RAS)
RESET_N: C28.2, C29.2, GPIO-1.5, R4.1, RESET_N144.P$1, U3.159 (RESET_N), U9.25 (PWROK)
SD0CARD-DETECT: RM12.4.2 (2), SD144.9 (CP_E), U3.155 (PG0/EINT0)
SDC0_CMD: JTAG144.5, R18.1, SD144.3 (CMD/DI), U3.111 (PF3/SDC0_CMD/JTAG_TDO)
SDC0_DATA0: JTAG144.2, RM12.2.2 (2), SD144.7 (DAT0/DO), U3.108 (PF1/SDC0_D0/JTAG_TDI)
SDC0_DATA1: JTAG144.3, RM12.3.2 (2), SD144.8 (DAT1/RES), U3.107 (PF0/SDC0_D1/JTAG_TMS)
SDC0_DATA2: JTAG144.4, RM12.1.2 (2), SD144.1 (DAT2/RES), U3.113 (PF5/SDC0_D2/JTAG_TCK)
SDC0_DATA3: R15.1, SD144.2 (CD/DAT3/CS), U3.112 (PF4/SDC0_D3/UART0_RX), UART0.3
SDC0_SCK: SD144.5 (CLK/SCLK), U3.110 (PF2/SDC0_CLK/UART0_TX), UART0.2
SD_VCC: C68.2, C69.2, L1.2, SD144.4 (VDD)
SPI2_CLK: U3.115 (PE1/CSI_MCLK/SPI2_CLK/EINT15), UEXT144.9
SPI2_CS0: R51.1, U3.114 (PE0/CSI_PCLK/SPI2_CS0/EINT14), UEXT144.10
SPI2_MISO: U3.117 (PE3/CSI_VSYNC/SPI2_MISO), UEXT144.7
SPI2_MOSI: U3.116 (PE2/CSI_HSYNC/SPI2_MOSI), UEXT144.8
SVREF: C1.2, C2.2, C37.2, R1.1, R2.2, U3.18 (SVREF)
TPX1: C61.2, LCD_CON144.37, U3.89 (TPX1)
TPX2: C66.2, LCD_CON144.38, U3.87 (TPX2)
TPY1: C65.2, LCD_CON144.39, U3.90 (TPY1)
TPY2: C67.2, LCD_CON144.40, U3.88 (TPY2)
TWI2_SCK: R49.1, U3.161 (PB17/TWI2_SCK), UEXT144.5
TWI2_SDA: R50.1, U3.160 (PB18/TWI2_SDA), UEXT144.6
UART1_RX: D11.1 (A1), R102.1, U3.151 (PG4/UART1_RX/EINT4), UEXT144.4
UART1_TX: U3.152 (PG3/UART1_TX/EINT3), UART1.2, UEXT144.3
UBOOT: R83.2, SW5.P$2 (1), U3.157 (UBOOT)
UDM0: U3.93 (UDM0), USB_OTG144.D-
UDM1: U3.95 (UDM1), U11.25 (DM0)
UDP0: U3.94 (UDP0), USB_OTG144.D+
UDP1: U3.96 (UDP1), U11.26 (DP0)
USB0-DRV: R67.2, U3.15 (PG12/SPI1_MISO/UART3_RTS/EINT12), U9.6 (N_VBUSEN), U12.4 (EN)
USB0-IDDET: R17.2, U3.153 (PG2/EINT2), USB_OTG144.ID
USB0-VBUSDET: C141.1, R64.1, R69.2, U3.154 (PG1/EINT1)
V+: 1.5V_E144.2, C1.1, C12.2, C13.2, C14.2, C15.2, C16.2, C30.1, C39.2, C40.2, C41.2, C42.2, C43.2, C44.2, C47.2, C48.2, C49.2, C50.2, C51.2, C52.2, P1.1, R1.2, R6.2, U1.A2 (VDD), U1.A9 (VDD), U1.B9 (VDDQ), U1.C1 (VDDQ), U1.D7 (VDD), U1.E2 (VDDQ), U1.E9 (VDDQ), U1.G2 (VDD), U1.G8 (VDD), U1.K1 (VDD), U1.K9 (VDD), U1.M1 (VDD), U1.M9 (VDD), U2.A2 (VDD), U2.A9 (VDD), U2.B9 (VDDQ), U2.C1 (VDDQ), U2.D7 (VDD), U2.E2 (VDDQ), U2.E9 (VDDQ), U2.G2 (VDD), U2.G8 (VDD), U2.K1 (VDD), U2.K9 (VDD), U2.M1 (VDD), U2.M9 (VDD), U3.23 (VCC1_DRAM), U3.30 (VCC2_DRAM), U3.43 (VCC3_DRAM), U3.53 (VCC4_DRAM), U3.62 (VCC5_DRAM)
VCC: 3.3V_E144.2, 3.3V_OPTION144.2, C3.2, C4.2, C17.2, C18.2, C36.2, C57.2, C70.2, C71.2, C80.1, C81.1, C82.1, D1.A, D2.2 (K), D3.2 (K), D4.2 (K), GPIO-1.3, GPIO-2.3, JTAG144.1, L1.1, LCD_CON144.3, P7.1, R4.2, R14.1, R16.1, R17.1, R18.2, R19.2, R47.1, R49.2, R50.2, R51.2, R60.2, R61.2, R75.2, R77.2, R97.1, R102.2, RM12.1.1 (1), RM12.2.1 (1), RM12.3.1 (1), RM12.4.1 (1), U3.5 (VCC1), U3.76 (V33_HP), U3.97 (V33_USB), U3.100 (VCC2), U3.142 (VCC3), U3.163 (VCC4), U4.12 (VCC), U4.37 (VCC), U5.20 (VCC), U6.20 (VCC), U7.20 (VCC), UART0.1, UART1.1, UEXT144.1
VCC/2: C5.2, C6.2, C7.2, C8.2, C19.2, C20.2, C21.2, C22.2, C83.1, C84.1, L3.2, P3.1, U3.4 (VDD1_CPU), U3.9 (VDD2_CPU), U3.11 (VDD3_CPU), U3.16 (VDD4_CPU), U3.156 (VDD5_CPU), U3.164 (VDD6_CPU), U3.169 (VDD7_CPU), U3.173 (VDD8_CPU), U9.10 (DCDC2)
VCCINT: C9.2, C10.2, C11.2, C23.2, C24.2, C86.1, C87.1, L4.2, P11.1, U3.35 (VDD1_INT), U3.73 (VDD2_INT), U3.98 (VDD3-INT), U3.109 (VDD4_INT), U3.149 (VDD5_INT), U9.17 (DCDC3)
VDD_RTC: C93.1, D10.1 (A1), P2.1, U9.28 (LDO1)
VGA_B: D4.3 (AK), R22.2, R26.2, R30.2, R33.2, R37.2, R40.2, VGA_DB15-F144.3 (F)
VGA_CTRL: FET4.3 (D), R19.1, R42.2, U5.1 (G), U5.19 (G), U6.1 (G), U6.19 (G), U7.1 (G), U7.19 (G)
VGA_G: D3.3 (AK), R21.2, R25.2, R29.2, R32.2, R36.2, R39.2, VGA_DB15-F144.2 (F)
VGA_HSYNC: D5.3 (AK), FET2.3 (D), R100.1, VGA_DB15-F144.13 (F)
VGA_R: D2.3 (AK), R20.2, R24.2, R28.2, R31.2, R35.2, R38.2, VGA_DB15-F144.1 (F)
VGA_VSYNC: D6.3 (AK), FET1.3 (D), R101.1, VGA_DB15-F144.14 (F)
VINT: C89.2, U9.26 (VINT), U9.27 (LDO1SET)
VMIC: C55.2, R9.1, U3.85 (VMIC)
VPP: C25.2, C96.1, P4.1, R76.1, U3.81 (AVCC), U9.12 (LDO2), U10.1 (EN)
WEN: RM5.4.2 (2), U1.H3 (#WE), U2.H3 (#WE)
WIFI-3V3: C100.1, U9.41 (LDO3), WIFI-3.3V/5V_USB144.3
X1: C120.2, Q2.2, U11.6 (X1)
X2: C125.2, Q2.1, U11.7 (X2)
XTALI: C26.2, Q1.2, U3.92 (X24MIN)
XTALO: C27.2, Q1.1, U3.91 (X24MOUT)

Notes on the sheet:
POWER SUPPLY CIRCUIT
LI-ION_BATTERY
2 x [2Gb DDR3 SDRAM (256Mx8)]
MicroSD
UEXT
Buttons
USB-OTG
USB-HOSTs
VCC
GND
RTC_MODULE
LED
NAND Flash
32Gb (4096M x 8bit)
GPIO EXTENSION
LCD EXTENSION
VGA
VOL+
VOL-
MENU
ENTER
HOME
JTAG
UART

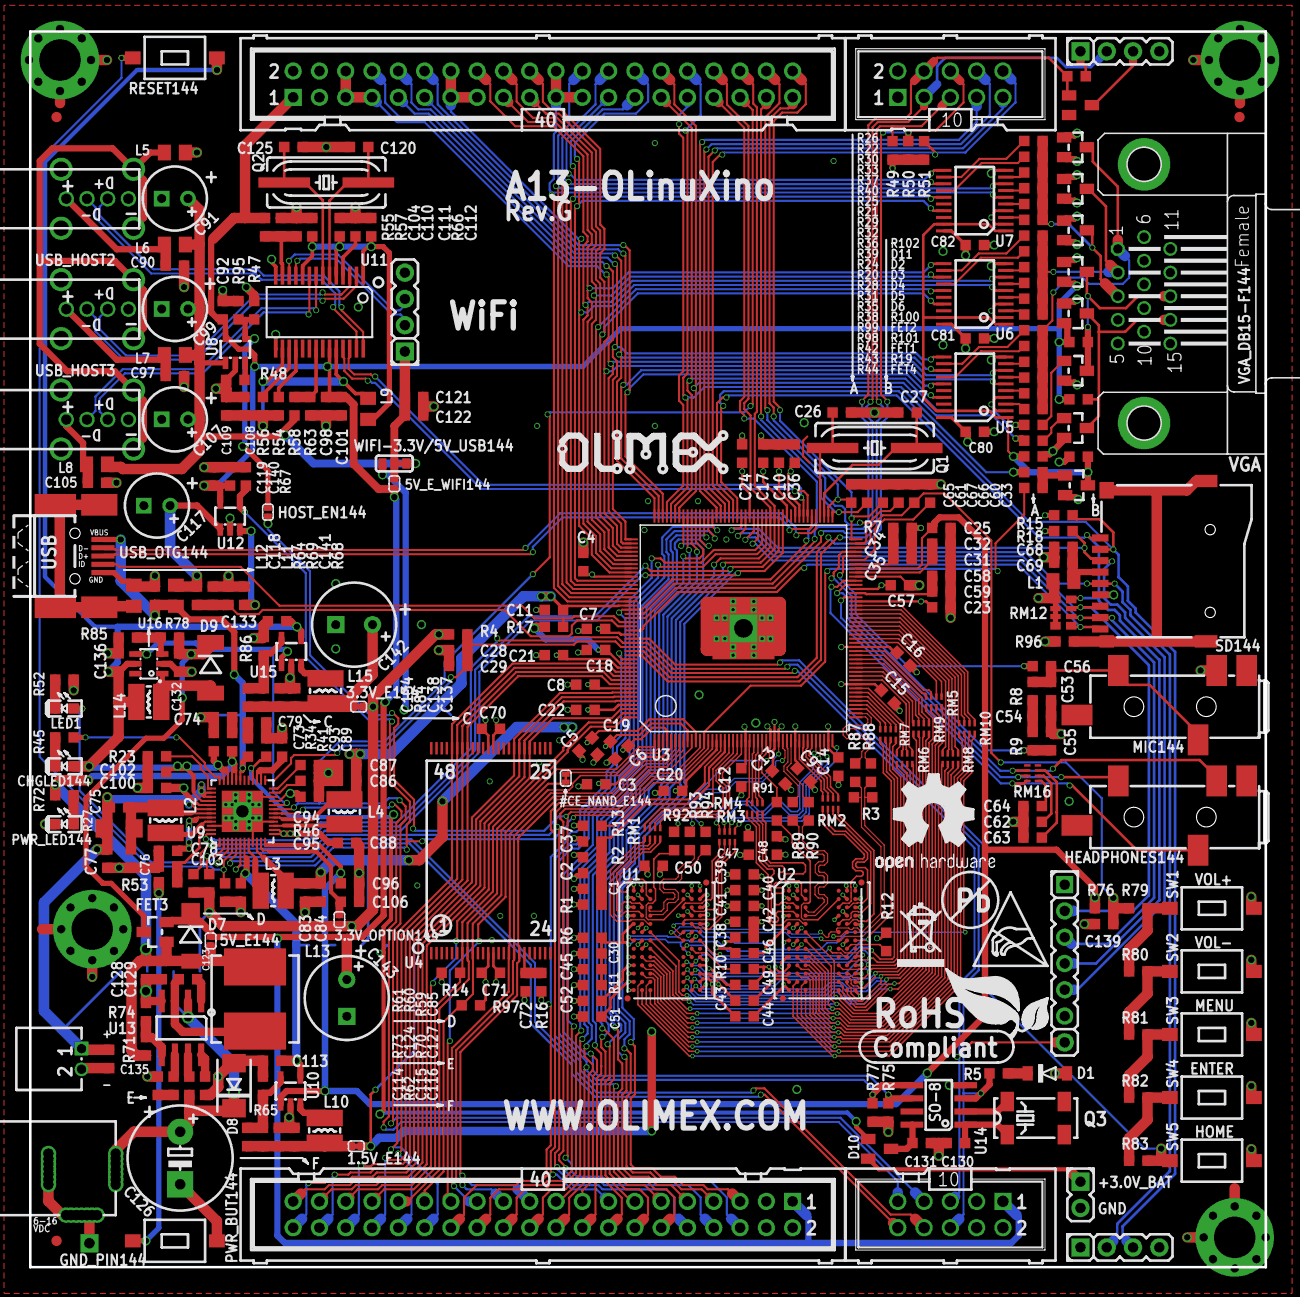
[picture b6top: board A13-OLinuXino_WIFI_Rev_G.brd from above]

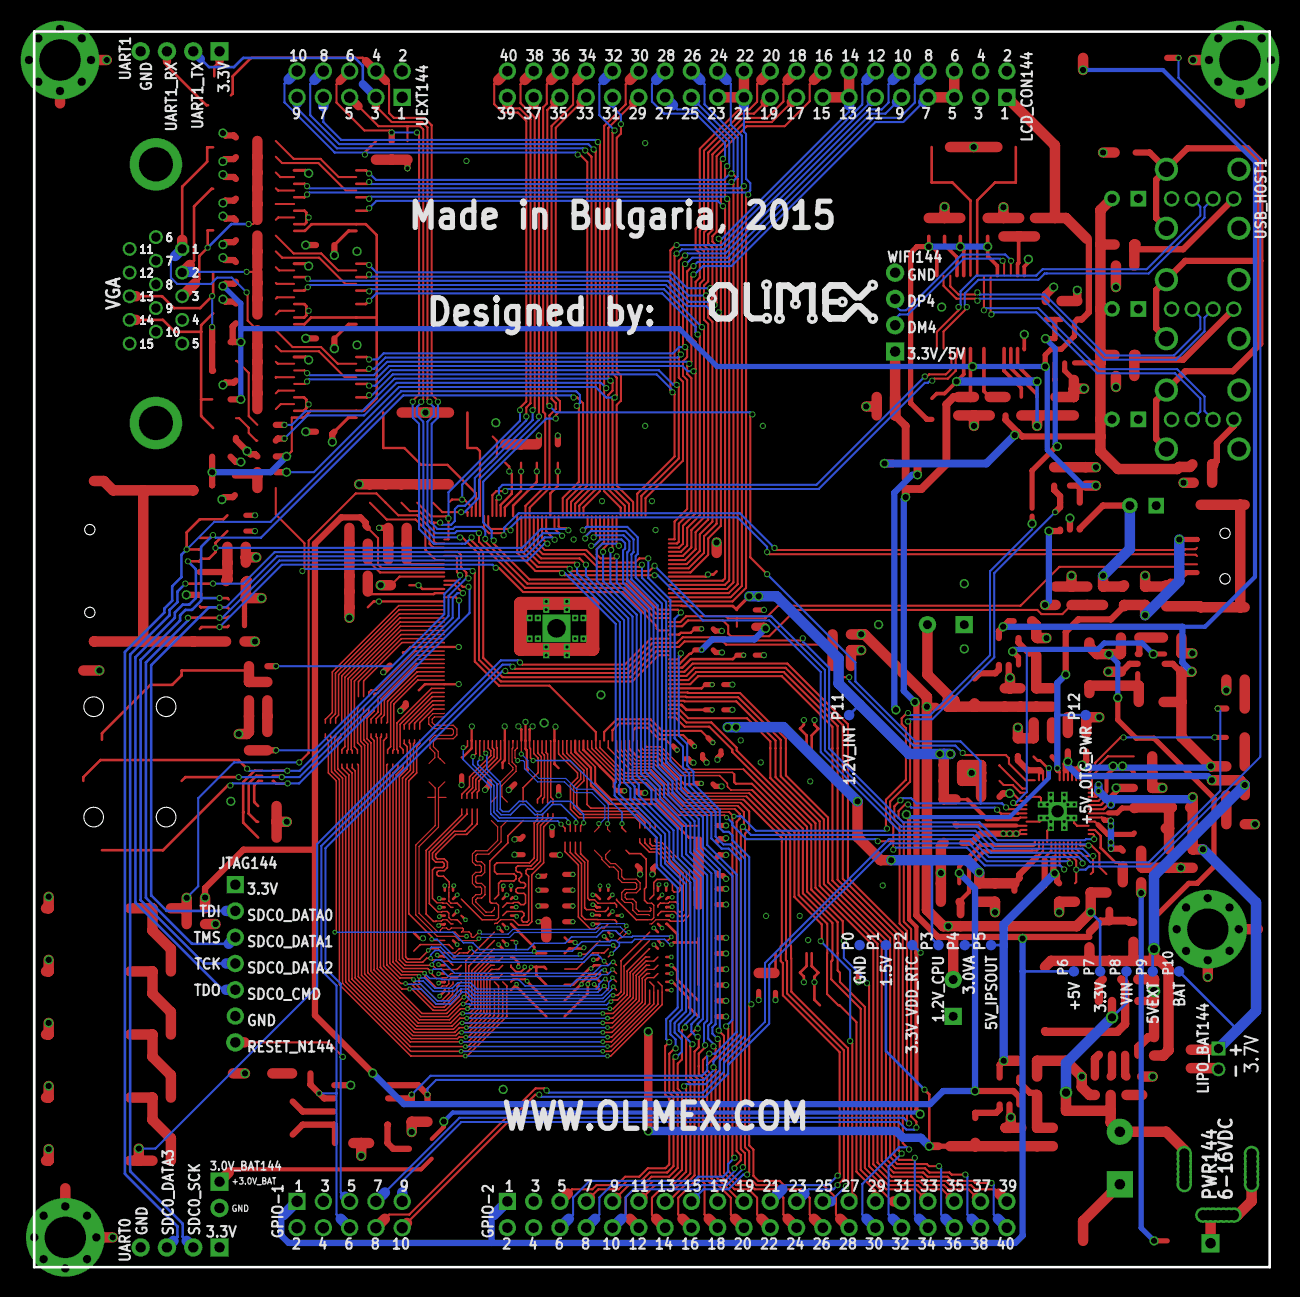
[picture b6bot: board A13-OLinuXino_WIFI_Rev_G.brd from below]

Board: 4 copper layers, 119.4 x 119.4 mm, 369 parts (14 on the bottom side), 327 nets.

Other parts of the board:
U$5: LOGO-OPENHARDWARE_8X8
U$6, U$8: OLIMEX1_V
U$9: PB
U$10: ESD_SYMBOL
U$11: RECYCLE_BIN1/8
U$12: ROHS
